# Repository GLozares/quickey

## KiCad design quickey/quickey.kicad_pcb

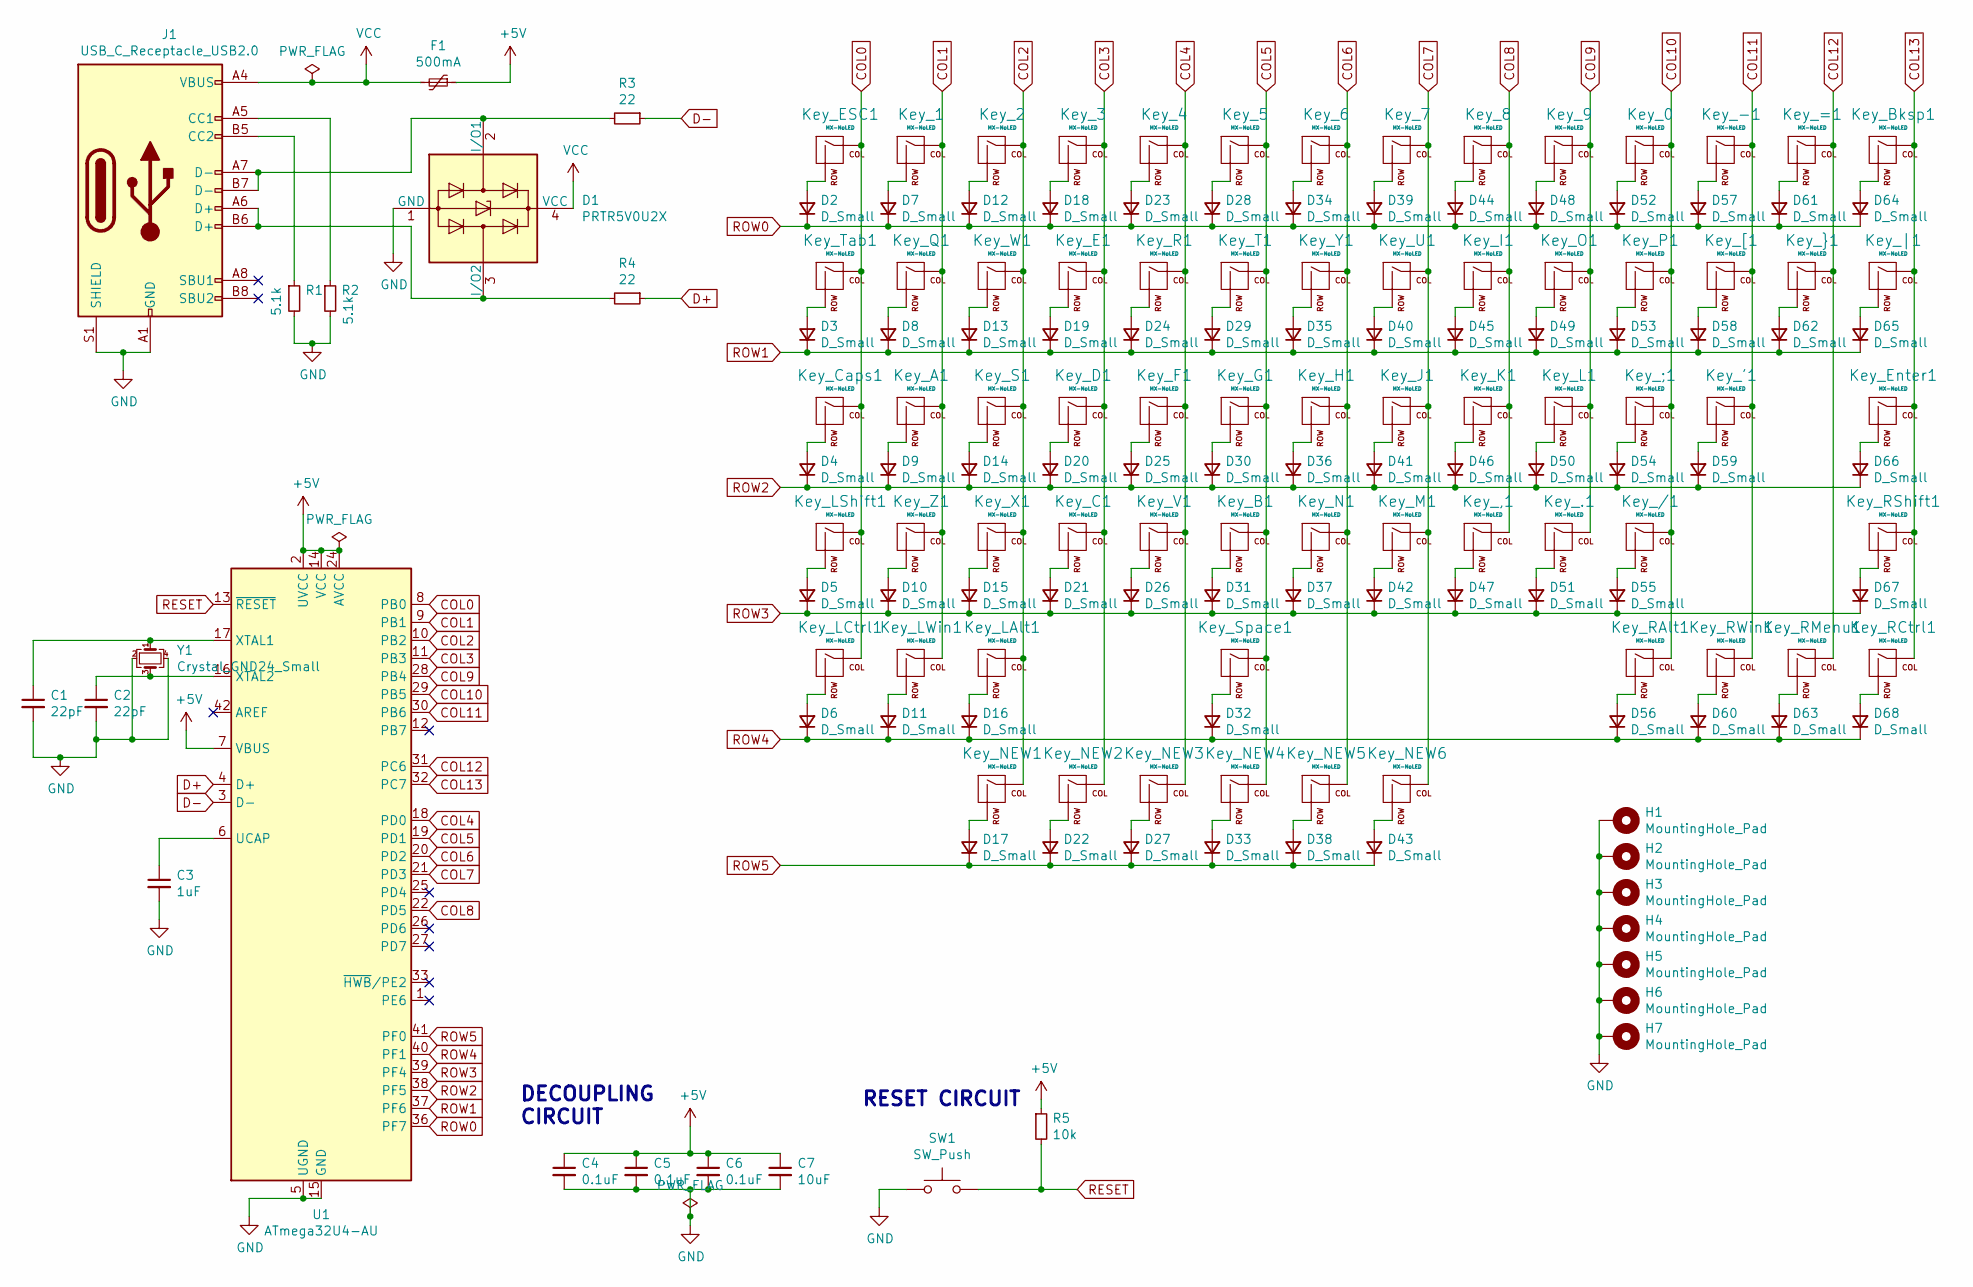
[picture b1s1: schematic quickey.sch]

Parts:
C1, C2: 22pF; C_0805_2012Metric
C3: 1uF; C_0805_2012Metric
C4, C5, C6: 0.1uF; C_0805_2012Metric
C7: 10uF; C_0805_2012Metric
D1: PRTR5V0U2X; SOT-143
D2, D3, D4, D5, D6, D7, D8, D9, D10, D11, D12, D13, D14, D15, D16, D17, D18, D19, D20, D21, D22, D23, D24, D25, D26, D27, D28, D29, D30, D31, D32, D33, D34, D35, D36, D37, D38, D39, D40, D41, D42, D43, D44, D45, D46, D47, D48, D49, D50, D51, D52, D53, D54, D55, D56, D57, D58, D59, D60, D61, D62, D63, D64, D65, D66, D67, D68: D_Small; D_SOD-123
F1: 500mA; Fuse_1812_4532Metric
H1, H2, H3, H4, H5, H6, H7: MountingHole_Pad; MountingHole_2.2mm_M2_Pad
J1: USB_C_Receptacle_USB2.0; USB_C_Receptacle_HRO_TYPE-C-31-M-12
Key_0, Key_1, Key_2, Key_3, Key_4, Key_5, Key_6, Key_7, Key_8, Key_9, Key_.1: MX-NoLED; MXOnly-1U
Key_'1: MX-NoLED; MXOnly-1U
Key_,1: MX-NoLED; MXOnly-1U
Key_-1: MX-NoLED; MXOnly-1U
Key_/1: MX-NoLED; MXOnly-1U
Key_;1: MX-NoLED; MXOnly-1U
Key_=1: MX-NoLED; MXOnly-1U
Key_A1: MX-NoLED; MXOnly-1U
Key_B1: MX-NoLED; MXOnly-1U
Key_Bksp1: MX-NoLED; MXOnly-2U
Key_C1: MX-NoLED; MXOnly-1U
Key_Caps1: MX-NoLED; MXOnly-1.75U
Key_D1: MX-NoLED; MXOnly-1U
Key_E1: MX-NoLED; MXOnly-1U
Key_ESC1: MX-NoLED; MXOnly-1U
Key_Enter1: MX-NoLED; MXOnly-2.25U
Key_F1: MX-NoLED; MXOnly-1U
Key_G1: MX-NoLED; MXOnly-1U
Key_H1: MX-NoLED; MXOnly-1U
Key_I1: MX-NoLED; MXOnly-1U
Key_J1: MX-NoLED; MXOnly-1U
Key_K1: MX-NoLED; MXOnly-1U
Key_L1: MX-NoLED; MXOnly-1U
Key_LAlt1: MX-NoLED; MXOnly-1.25U
Key_LCtrl1: MX-NoLED; MXOnly-1.25U
Key_LShift1: MX-NoLED; MXOnly-2.25U
Key_LWin1: MX-NoLED; MXOnly-1.25U
Key_M1: MX-NoLED; MXOnly-1U
Key_N1: MX-NoLED; MXOnly-1U
Key_NEW1, Key_NEW2, Key_NEW3, Key_NEW4, Key_NEW5, Key_NEW6: MX-NoLED; MXOnly-1U
Key_O1: MX-NoLED; MXOnly-1U
Key_P1: MX-NoLED; MXOnly-1U
Key_Q1: MX-NoLED; MXOnly-1U
Key_R1: MX-NoLED; MXOnly-1U
Key_RAlt1: MX-NoLED; MXOnly-1.25U
Key_RCtrl1: MX-NoLED; MXOnly-1.25U
Key_RMenu1: MX-NoLED; MXOnly-1.25U
Key_RShift1: MX-NoLED; MXOnly-2.75U
Key_RWin1: MX-NoLED; MXOnly-1.25U
Key_S1: MX-NoLED; MXOnly-1U
Key_Space1: MX-NoLED; MXOnly-6.25U
Key_T1: MX-NoLED; MXOnly-1U
Key_Tab1: MX-NoLED; MXOnly-1.5U
Key_U1: MX-NoLED; MXOnly-1U
Key_V1: MX-NoLED; MXOnly-1U
Key_W1: MX-NoLED; MXOnly-1U
Key_X1: MX-NoLED; MXOnly-1U
Key_Y1: MX-NoLED; MXOnly-1U
Key_Z1: MX-NoLED; MXOnly-1U
Key_[1: MX-NoLED; MXOnly-1U
Key_|1: MX-NoLED; MXOnly-1.5U
Key_}1: MX-NoLED; MXOnly-1U
R1, R2: 5.1k; R_0805_2012Metric
R3, R4: 22; R_0805_2012Metric
R5: 10k; R_0805_2012Metric
SW1: SW_Push; SW_SPST_SKQG_WithoutStem
U1: ATmega32U4-AU; TQFP-44_10x10mm_P0.8mm
Y1: Crystal_GND24_Small; Crystal_SMD_3225-4Pin_3.2x2.5mm

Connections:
+5V: C4.1, C5.1, C6.1, C7.1, F1.1, R5.1, U1.2 (UVCC), U1.7 (VBUS), U1.14 (VCC), U1.24 (AVCC), U1.34 (VCC), U1.44 (AVCC)
COL0: Key_Caps1.1 (COL), Key_ESC1.1 (COL), Key_LCtrl1.1 (COL), Key_LShift1.1 (COL), Key_Tab1.1 (COL), U1.8 (PB0)
COL1: Key_1.1 (COL), Key_A1.1 (COL), Key_LWin1.1 (COL), Key_Q1.1 (COL), Key_Z1.1 (COL), U1.9 (PB1)
COL2: Key_2.1 (COL), Key_LAlt1.1 (COL), Key_NEW1.1 (COL), Key_S1.1 (COL), Key_W1.1 (COL), Key_X1.1 (COL), U1.10 (PB2)
COL3: Key_3.1 (COL), Key_C1.1 (COL), Key_D1.1 (COL), Key_E1.1 (COL), Key_NEW2.1 (COL), U1.11 (PB3)
COL4: Key_4.1 (COL), Key_F1.1 (COL), Key_NEW3.1 (COL), Key_R1.1 (COL), Key_V1.1 (COL), U1.18 (PD0)
COL5: Key_5.1 (COL), Key_B1.1 (COL), Key_G1.1 (COL), Key_NEW4.1 (COL), Key_Space1.1 (COL), Key_T1.1 (COL), U1.19 (PD1)
COL6: Key_6.1 (COL), Key_H1.1 (COL), Key_N1.1 (COL), Key_NEW5.1 (COL), Key_Y1.1 (COL), U1.20 (PD2)
COL7: Key_7.1 (COL), Key_J1.1 (COL), Key_M1.1 (COL), Key_NEW6.1 (COL), Key_U1.1 (COL), U1.21 (PD3)
COL8: Key_8.1 (COL), Key_,1.1 (COL), Key_I1.1 (COL), Key_K1.1 (COL), U1.22 (PD5)
COL9: Key_9.1 (COL), Key_.1.1 (COL), Key_L1.1 (COL), Key_O1.1 (COL), U1.28 (PB4)
COL10: Key_0.1 (COL), Key_/1.1 (COL), Key_;1.1 (COL), Key_P1.1 (COL), Key_RAlt1.1 (COL), U1.29 (PB5)
COL11: Key_'1.1 (COL), Key_-1.1 (COL), Key_RWin1.1 (COL), Key_[1.1 (COL), U1.30 (PB6)
COL12: Key_=1.1 (COL), Key_RMenu1.1 (COL), Key_}1.1 (COL), U1.31 (PC6)
COL13: Key_Bksp1.1 (COL), Key_Enter1.1 (COL), Key_RCtrl1.1 (COL), Key_RShift1.1 (COL), Key_|1.1 (COL), U1.32 (PC7)
D+: R4.1, U1.4 (D+)
D-: R3.1, U1.3 (D-)
GND: C1.2, C2.2, C3.2, C4.2, C5.2, C6.2, C7.2, D1.1 (GND), H1.1, H2.1, H3.1, H4.1, H5.1, H6.1, H7.1, J1.A1 (GND), J1.A12 (GND), J1.B1 (GND), J1.B12 (GND), J1.S1 (SHIELD), R1.2, R2.2, SW1.1, U1.5 (UGND), U1.15 (GND), U1.23 (GND), U1.35 (GND), U1.43 (GND), Y1.2, Y1.4
unnamed: C1.1, U1.17 (XTAL1), Y1.1
unnamed: C2.1, U1.16 (XTAL2), Y1.3
unnamed: C3.1, U1.6 (UCAP)
unnamed: D1.2 (I/O1), J1.A7 (D-), J1.B7 (D-), R3.2
unnamed: D1.3 (I/O2), J1.A6 (D+), J1.B6 (D+), R4.2
unnamed: D2.2 (A), Key_ESC1.2 (ROW)
unnamed: D3.2 (A), Key_Tab1.2 (ROW)
unnamed: D4.2 (A), Key_Caps1.2 (ROW)
unnamed: D5.2 (A), Key_LShift1.2 (ROW)
unnamed: D6.2 (A), Key_LCtrl1.2 (ROW)
unnamed: D7.2 (A), Key_1.2 (ROW)
unnamed: D8.2 (A), Key_Q1.2 (ROW)
unnamed: D9.2 (A), Key_A1.2 (ROW)
unnamed: D10.2 (A), Key_Z1.2 (ROW)
unnamed: D11.2 (A), Key_LWin1.2 (ROW)
unnamed: D12.2 (A), Key_2.2 (ROW)
unnamed: D13.2 (A), Key_W1.2 (ROW)
unnamed: D14.2 (A), Key_S1.2 (ROW)
unnamed: D15.2 (A), Key_X1.2 (ROW)
unnamed: D16.2 (A), Key_LAlt1.2 (ROW)
unnamed: D17.2 (A), Key_NEW1.2 (ROW)
unnamed: D18.2 (A), Key_3.2 (ROW)
unnamed: D19.2 (A), Key_E1.2 (ROW)
unnamed: D20.2 (A), Key_D1.2 (ROW)
unnamed: D21.2 (A), Key_C1.2 (ROW)
unnamed: D22.2 (A), Key_NEW2.2 (ROW)
unnamed: D23.2 (A), Key_4.2 (ROW)
unnamed: D24.2 (A), Key_R1.2 (ROW)
unnamed: D25.2 (A), Key_F1.2 (ROW)
unnamed: D26.2 (A), Key_V1.2 (ROW)
unnamed: D27.2 (A), Key_NEW3.2 (ROW)
unnamed: D28.2 (A), Key_5.2 (ROW)
unnamed: D29.2 (A), Key_T1.2 (ROW)
unnamed: D30.2 (A), Key_G1.2 (ROW)
unnamed: D31.2 (A), Key_B1.2 (ROW)
unnamed: D32.2 (A), Key_Space1.2 (ROW)
unnamed: D33.2 (A), Key_NEW4.2 (ROW)
unnamed: D34.2 (A), Key_6.2 (ROW)
unnamed: D35.2 (A), Key_Y1.2 (ROW)
unnamed: D36.2 (A), Key_H1.2 (ROW)
unnamed: D37.2 (A), Key_N1.2 (ROW)
unnamed: D38.2 (A), Key_NEW5.2 (ROW)
unnamed: D39.2 (A), Key_7.2 (ROW)
unnamed: D40.2 (A), Key_U1.2 (ROW)
unnamed: D41.2 (A), Key_J1.2 (ROW)
unnamed: D42.2 (A), Key_M1.2 (ROW)
unnamed: D43.2 (A), Key_NEW6.2 (ROW)
unnamed: D44.2 (A), Key_8.2 (ROW)
unnamed: D45.2 (A), Key_I1.2 (ROW)
unnamed: D46.2 (A), Key_K1.2 (ROW)
unnamed: D47.2 (A), Key_,1.2 (ROW)
unnamed: D48.2 (A), Key_9.2 (ROW)
unnamed: D49.2 (A), Key_O1.2 (ROW)
unnamed: D50.2 (A), Key_L1.2 (ROW)
unnamed: D51.2 (A), Key_.1.2 (ROW)
unnamed: D52.2 (A), Key_0.2 (ROW)
unnamed: D53.2 (A), Key_P1.2 (ROW)
unnamed: D54.2 (A), Key_;1.2 (ROW)
unnamed: D55.2 (A), Key_/1.2 (ROW)
unnamed: D56.2 (A), Key_RAlt1.2 (ROW)
unnamed: D57.2 (A), Key_-1.2 (ROW)
unnamed: D58.2 (A), Key_[1.2 (ROW)
unnamed: D59.2 (A), Key_'1.2 (ROW)
unnamed: D60.2 (A), Key_RWin1.2 (ROW)
unnamed: D61.2 (A), Key_=1.2 (ROW)
unnamed: D62.2 (A), Key_}1.2 (ROW)
unnamed: D63.2 (A), Key_RMenu1.2 (ROW)
unnamed: D64.2 (A), Key_Bksp1.2 (ROW)
unnamed: D65.2 (A), Key_|1.2 (ROW)
unnamed: D66.2 (A), Key_Enter1.2 (ROW)
unnamed: D67.2 (A), Key_RShift1.2 (ROW)
unnamed: D68.2 (A), Key_RCtrl1.2 (ROW)
unnamed: J1.A5 (CC1), R2.1
unnamed: J1.B5 (CC2), R1.1
RESET: R5.2, SW1.2, U1.13 (~RESET)
ROW0: D2.1 (K), D7.1 (K), D12.1 (K), D18.1 (K), D23.1 (K), D28.1 (K), D34.1 (K), D39.1 (K), D44.1 (K), D48.1 (K), D52.1 (K), D57.1 (K), D61.1 (K), D64.1 (K), U1.36 (PF7)
ROW1: D3.1 (K), D8.1 (K), D13.1 (K), D19.1 (K), D24.1 (K), D29.1 (K), D35.1 (K), D40.1 (K), D45.1 (K), D49.1 (K), D53.1 (K), D58.1 (K), D62.1 (K), D65.1 (K), U1.37 (PF6)
ROW2: D4.1 (K), D9.1 (K), D14.1 (K), D20.1 (K), D25.1 (K), D30.1 (K), D36.1 (K), D41.1 (K), D46.1 (K), D50.1 (K), D54.1 (K), D59.1 (K), D66.1 (K), U1.38 (PF5)
ROW3: D5.1 (K), D10.1 (K), D15.1 (K), D21.1 (K), D26.1 (K), D31.1 (K), D37.1 (K), D42.1 (K), D47.1 (K), D51.1 (K), D55.1 (K), D67.1 (K), U1.39 (PF4)
ROW4: D6.1 (K), D11.1 (K), D16.1 (K), D32.1 (K), D56.1 (K), D60.1 (K), D63.1 (K), D68.1 (K), U1.40 (PF1)
ROW5: D17.1 (K), D22.1 (K), D27.1 (K), D33.1 (K), D38.1 (K), D43.1 (K), U1.41 (PF0)
VCC: D1.4 (VCC), F1.2, J1.A4 (VBUS), J1.A9 (VBUS), J1.B4 (VBUS), J1.B9 (VBUS)

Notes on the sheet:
RESET CIRCUIT
DECOUPLING CIRCUIT

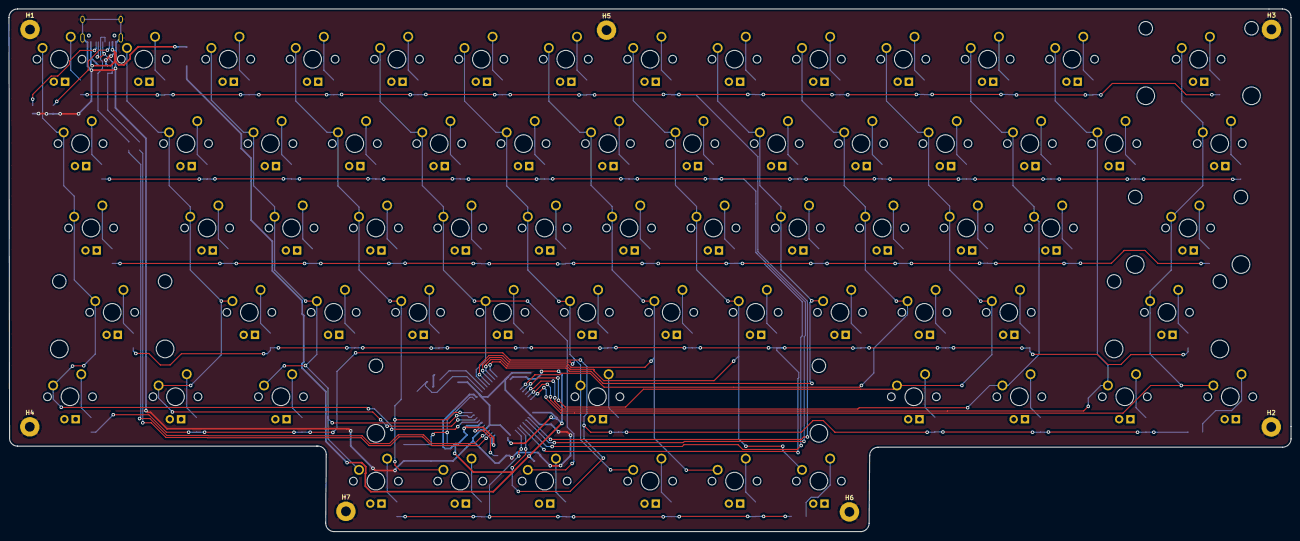
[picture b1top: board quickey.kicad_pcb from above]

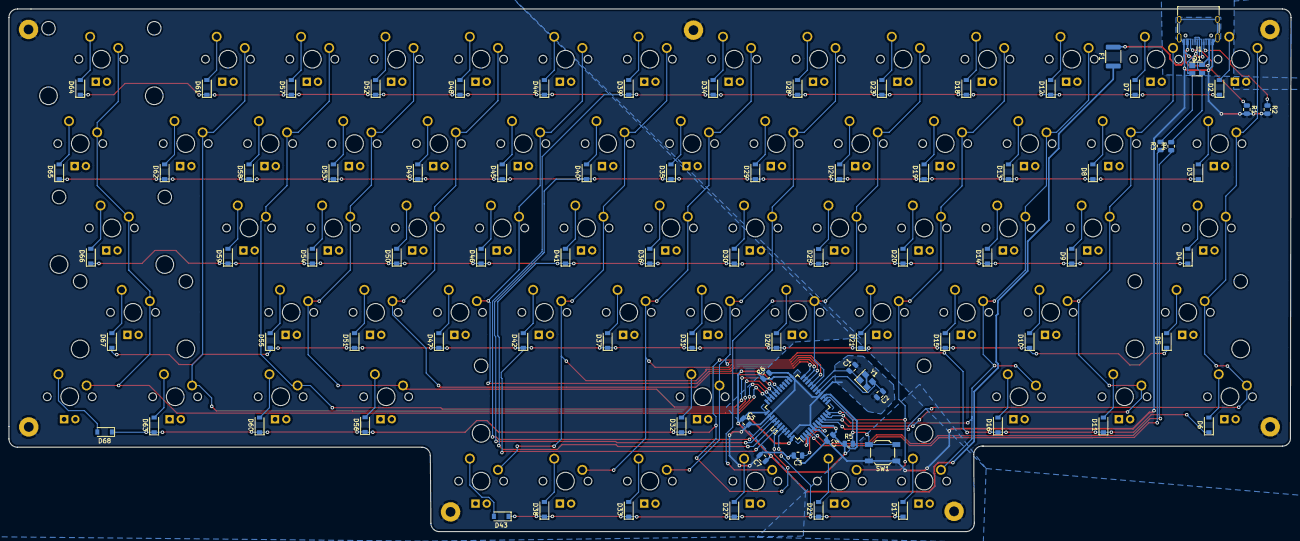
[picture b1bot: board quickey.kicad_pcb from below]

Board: 2 copper layers, 289.4 x 118.0 mm, 159 parts (85 on the bottom side), 100 nets.

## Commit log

2021-04-26 initial project creation
2021-04-26 added footprints
2021-04-26 Schematic and PCB
2021-04-26 Pass DRC ERC
2021-04-26 3d models
